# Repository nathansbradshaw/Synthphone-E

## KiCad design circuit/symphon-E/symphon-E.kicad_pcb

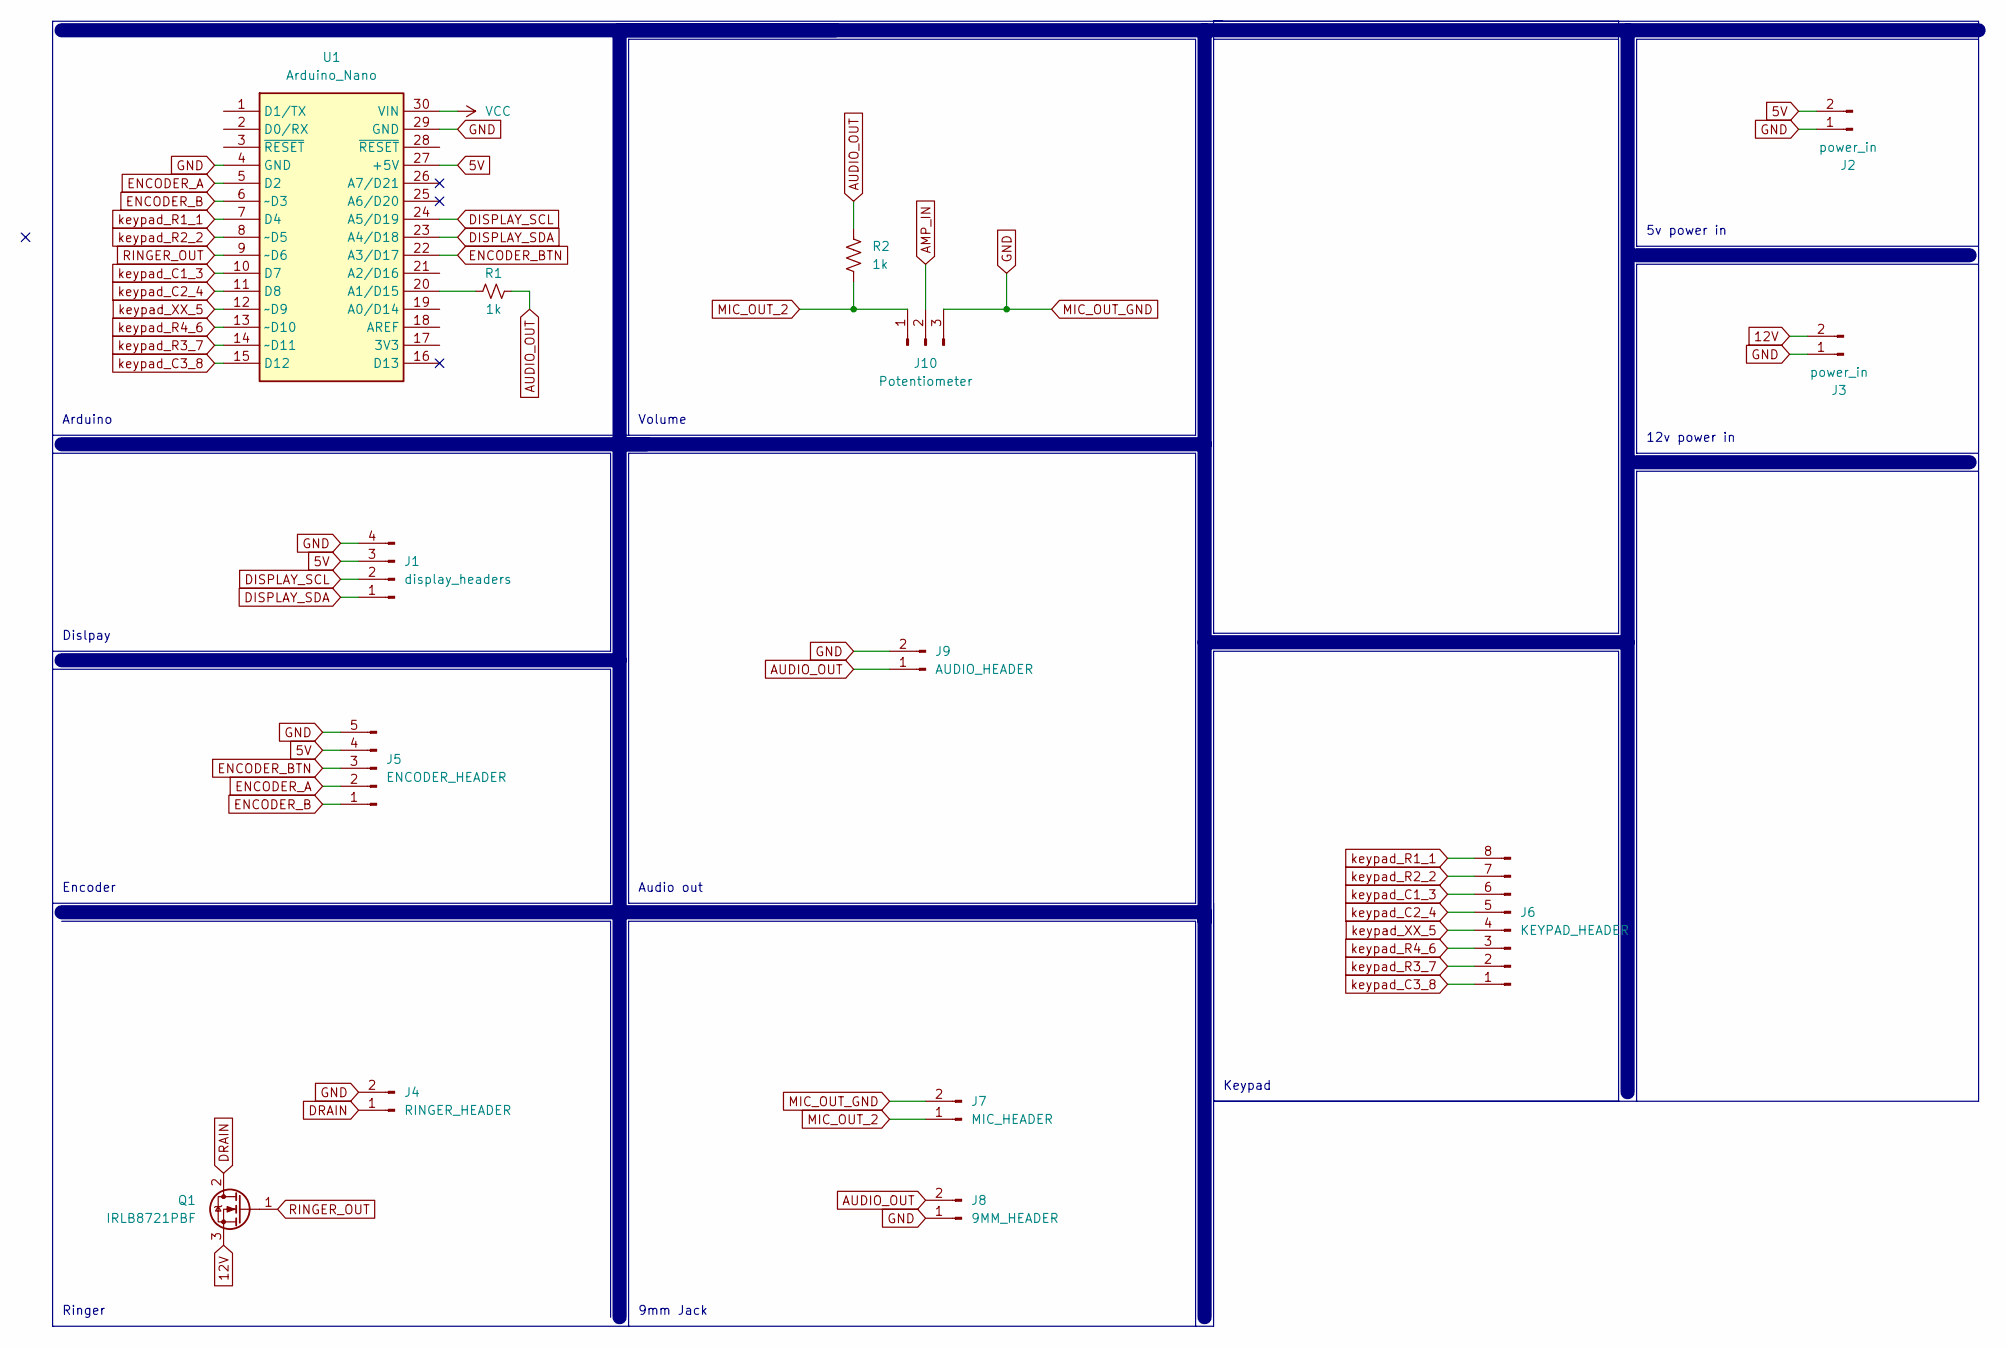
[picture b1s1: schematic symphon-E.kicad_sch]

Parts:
J1: display_headers; JST_EH_B4B-EH-A_1x04_P2.50mm_Vertical
J2, J3: power_in; JST_EH_B2B-EH-A_1x02_P2.50mm_Vertical
J4: RINGER_HEADER; JST_EH_B2B-EH-A_1x02_P2.50mm_Vertical
J5: ENCODER_HEADER; JST_EH_B5B-EH-A_1x05_P2.50mm_Vertical
J6: KEYPAD_HEADER; JST_EH_B8B-EH-A_1x08_P2.50mm_Vertical
J7: MIC_HEADER; JST_EH_B2B-EH-A_1x02_P2.50mm_Vertical
J8: 9MM_HEADER; JST_EH_B2B-EH-A_1x02_P2.50mm_Vertical
J9: AUDIO_HEADER; JST_EH_B2B-EH-A_1x02_P2.50mm_Vertical
J10: Potentiometer; JST_EH_B3B-EH-A_1x03_P2.50mm_Vertical
Q1: IRLB8721PBF; TO-220-3_Vertical
R1, R2: 1k; R_Axial_DIN0204_L3.6mm_D1.6mm_P7.62mm_Horizontal
U1: Arduino_Nano

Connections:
5V: J1.3, J2.2, J5.4, U1.27 (+5V)
12V: J3.2, Q1.3 (S)
AMP_IN: J10.2
AUDIO_OUT: J8.2, J9.1, R1.2, R2.1
DISPLAY_SCL: J1.2, U1.24 (A5/D19)
DISPLAY_SDA: J1.1, U1.23 (A4/D18)
DRAIN: J4.1, Q1.2 (D)
ENCODER_A: J5.2, U1.5 (D2)
ENCODER_B: J5.1, U1.6 (~D3)
ENCODER_BTN: J5.3, U1.22 (A3/D17)
GND: J1.4, J2.1, J3.1, J4.2, J5.5, J7.2, J8.1, J9.2, J10.3, U1.4 (GND), U1.29 (GND)
MIC_OUT_2: J7.1, J10.1, R2.2
unnamed: R1.1, U1.20 (A1/D15)
RINGER_OUT: Q1.1 (G), U1.9 (~D6)
VCC: U1.30 (VIN)
keypad_C1_3: J6.6, U1.10 (D7)
keypad_C2_4: J6.5, U1.11 (D8)
keypad_C3_8: J6.1, U1.15 (D12)
keypad_R1_1: J6.8, U1.7 (D4)
keypad_R2_2: J6.7, U1.8 (~D5)
keypad_R3_7: J6.2, U1.14 (~D11)
keypad_R4_6: J6.3, U1.13 (~D10)
keypad_XX_5: J6.4, U1.12 (~D9)

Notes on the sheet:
9mm Jack
5v power in
12v power in
Arduino
Ringer
Dislpay
Volume
Encoder
Audio out
Keypad

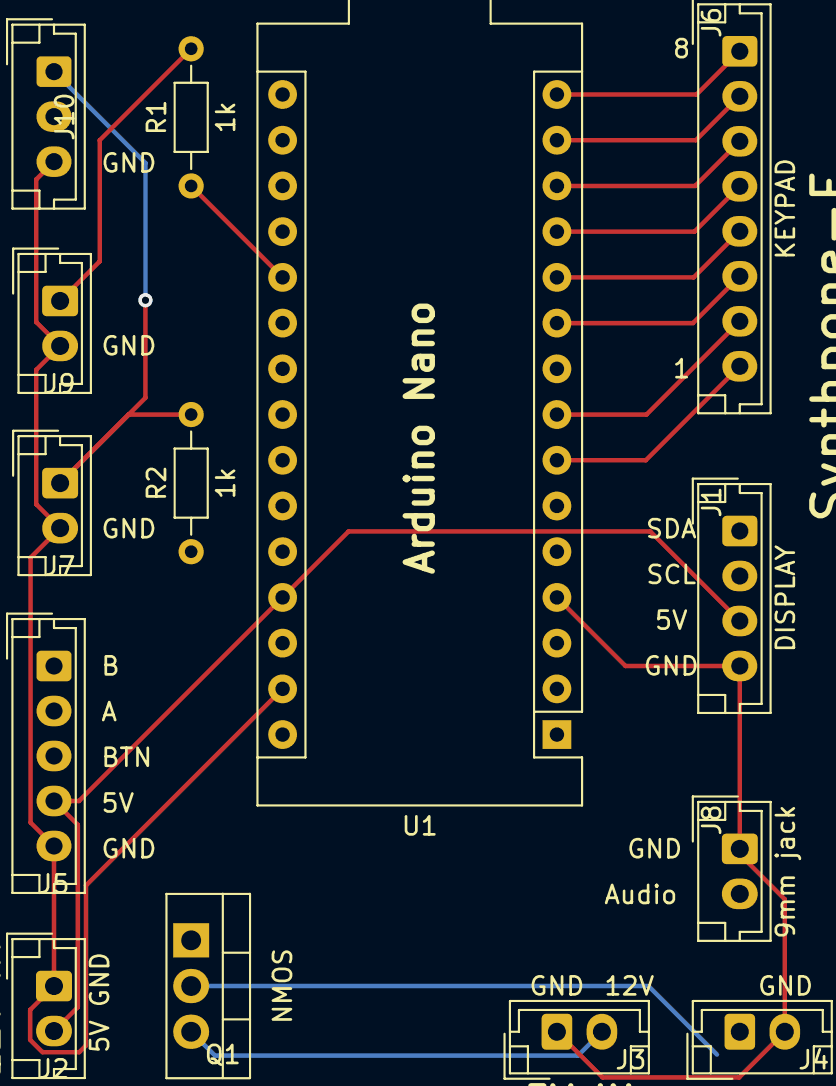
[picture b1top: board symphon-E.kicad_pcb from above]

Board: 2 copper layers, 14 parts (0 on the bottom side), 21 nets.

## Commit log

2022-08-04 init
2022-08-11 add pseudo code
2022-08-11 start on rotary input
2022-08-15 add in notes and names
2022-08-15 start fixing compile issues
2022-08-15 rotarty example
2022-08-18 fix rotary test
2022-08-18 add each of the different menu modes
2022-08-18 comment for later
2022-08-22 Note Recalculation
2022-09-01 fix bugs and logical fallacy
2022-09-01 fix more logic flaws, add in untested ringer code
2022-09-01 try to fix ringer
2022-09-08 add png
2022-09-15 moar code n stuff (started to add the display)
2022-09-29 add pinout
2022-09-29 split out the spritesheets and fix the display
2022-10-10 Clean up code
2022-10-10 ASCII ART
2022-10-10 part 2
2022-10-10 add pcb
2022-10-10 update pcb
2022-10-13 add tone library that supports volume
2022-10-13 update schematic
2023-02-05 add tests
